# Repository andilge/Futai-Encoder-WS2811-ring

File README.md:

# A sparkfun enlighted RGB rotary encoder and a ring of 12 WS2811 F5 LEDs behind a translucent blank cover panel
The ultimate DIY human light controller interface plenty of colored LEDs.

## Credits
Inspired by [isotope-engineering's RGB rotary encoder](https://github.com/isotope-engineering/RGB-Encoder-Board "isotope-engineering's RGB rotary encoder").

Shoutout to [ezcGman](https://github.com/ezcGman "ezcGman") for the assistance with the KiCad symbols and footprints, hints about thermal reliefs on pads and the continuous feedback about his experiences while building up the circuit with the board.

## KiCad dependencies
This project uses custom KiCad symbols and footprints and 3D models. Follow folder 'libs' with all details.

## Parts list
The folder 'fabrication' contains the zipped production files for pcb ordering and interactive bill of material ibom.html with purchase links for the components.

Additional to this you can purchase 10 blank cover panels on [aliexpress.com](https://www.aliexpress.com/item/32884601740.html "aliexpress.com")

### SPECIAL ATTENTION REQUIRED !
*There are reports about wrong pin out for the addressable LEDs (D1-D12)*

The [official data sheet from the producer](http://cn.world-semi.com/DownLoadFile/98 "official data sheet from the producer") says
|  pin # |   description   |
|:------:|:---------------:|
|   1    |       DOUT      |
|   2    |       VCC       |
|   3    |       GND       |
|   4    |       DIN       |

With the purchase URL in the BOM, you might get LEDs with 180 degree flipped around pin out
|  pin # |   description   |
|:------:|:---------------:|
|   1    |       DIN       |
|   2    |       GND       |
|   3    |       VCC       |
|   4    |       DOUT      |

If you solder these faulty LEDs on the board "the right way around" the following will happen:
No light turns on and the LEDs instantly burn off to nirvana, some with, others without magic smoke :astonished: rip

The board continues following the LED's specification and can handle these faulty LEDs if you just place them "the wrong way around". Basically, flipped pins together with flipped placement turns out as success again :man_facepalming:.

**IMPORTANT**: Please test a LED from the sent bunch first to get a reality approach about which way around you should use them !

Special thanks to [ezcGman](https://github.com/ezcGman "ezcGman") for burning time and components to achieve this particular insight.

## Connector pinout
| silkscreen | description                                                                                |
|:----------:|--------------------------------------------------------------------------------------------|
| 5V         | 5 Volt                                                                                     |
| GND        | Ground                                                                                     |
| EncA       | Encoder A                                                                                  |
| EncB       | Encoder B                                                                                  |
| SW         | Switch. On pressing the switch, 3.3 Volt are being passed to this header pin.              |
| RED        | High voltage level red channel for the rotary encoder LED. *See more information below !   |
| GRE        | High voltage level green channel for the rotary encoder LED. *See more information below ! |
| BLU        | High voltage level blue channel for the rotary encoder LED. *See more information below !  |
| Din        | Data bus in for the adressable LEDs                                                        |
| Dout       | Data bus out for the adressable LEDs                                                       |

*For compatibility reasons with RGB strips, the board exptects 24V (also dimmed with pwm) at the rgb pin headers. If you're driving your **strip with 12V**, please change the value for **R51, R61 and R71 to 5.1kΩ**.

## Schematic
Dive deeper into technical details in the folder 'datasheets-and-schematic'.

## Tools list
### Required
- A soldering iron
- Solder

### Optional
- For SMD components and addressable LEDs:
  - A hot air soldering/re-flow station. However, the smallest parts are 0805 SMD components which can be soldered with a soldering iron. The LED's legs are very close together and easier to solder with hot air.
  - Solder paste
- Tweezers
- The famous IKEA cork coaster (Onderzetter) that gently takes up the heat of your soldering tools.

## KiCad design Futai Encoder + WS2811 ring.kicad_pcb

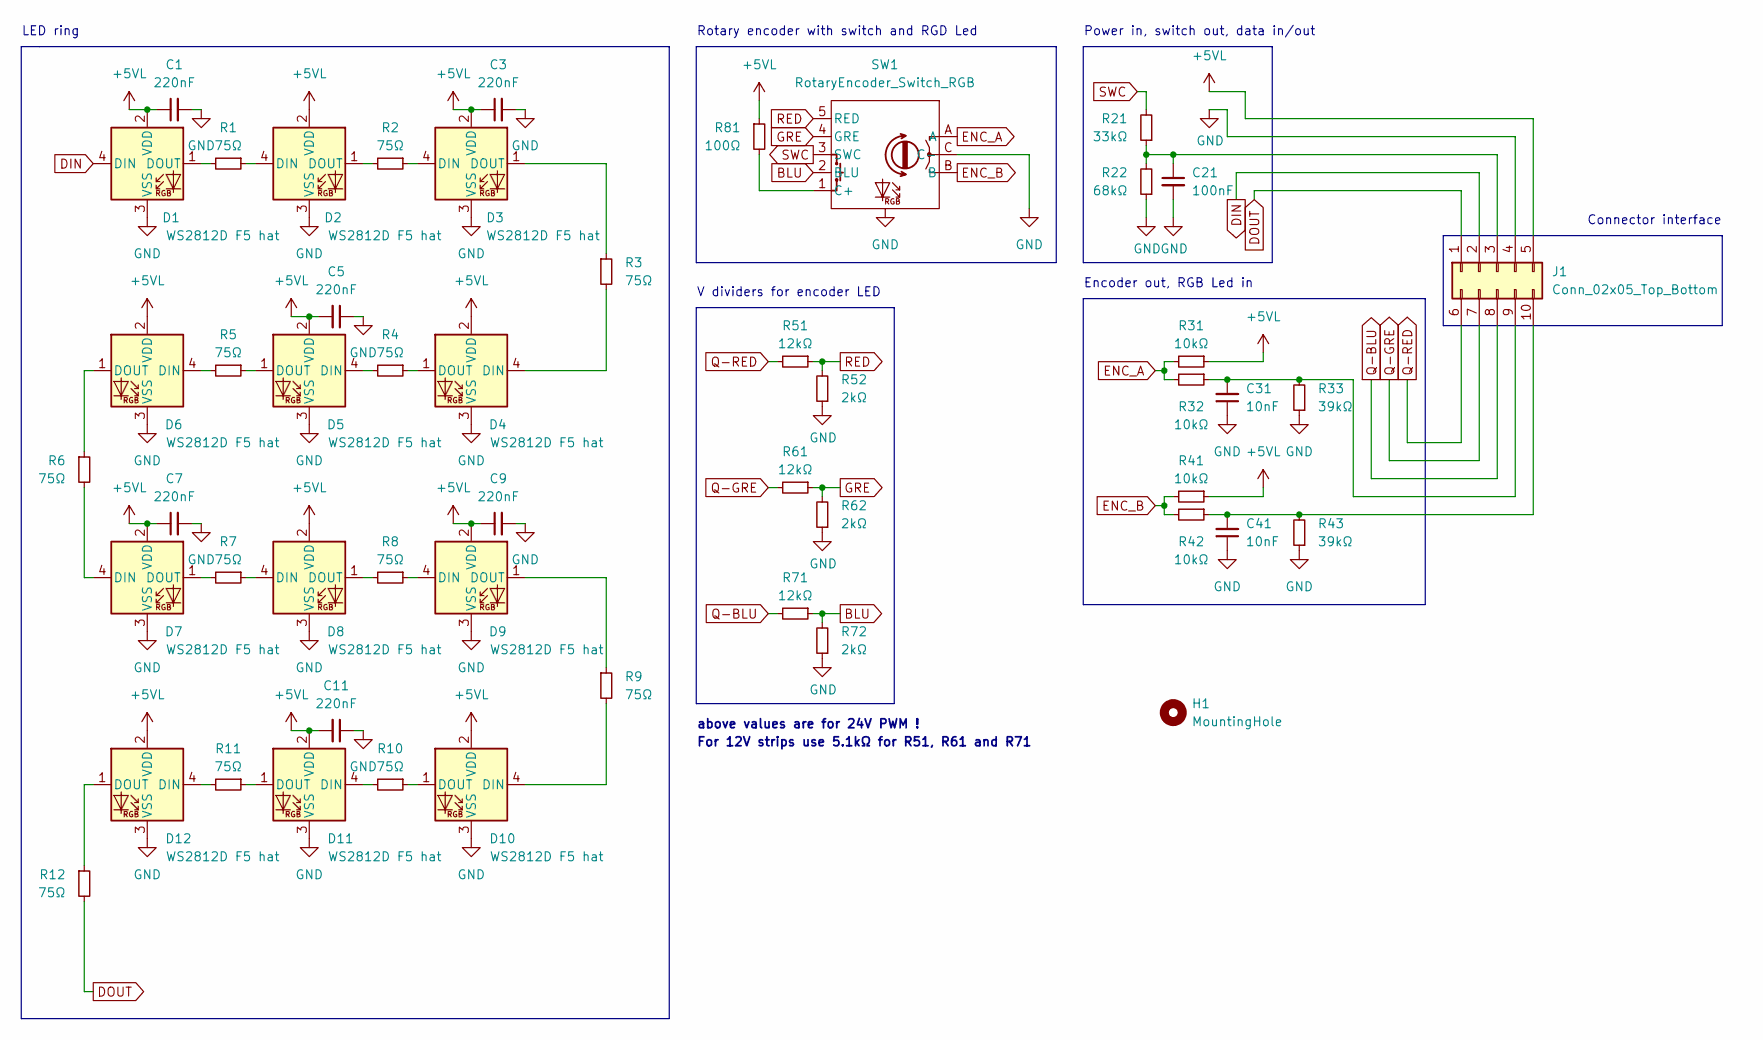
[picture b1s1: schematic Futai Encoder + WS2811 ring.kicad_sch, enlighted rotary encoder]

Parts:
C1, C3, C5, C7, C9, C11: 220nF; C_0805_2012Metric
C21: 100nF; C_0805_2012Metric
C31, C41: 10nF; C_0805_2012Metric
D1, D2, D3, D4, D5, D6, D7, D8, D9, D10, D11, D12: WS2812D F5 hat; WS2811D-F5-1261
H1: MountingHole; MountingHole_2.2mm_M2
J1: Conn_02x05_Top_Bottom; PinHeader_2x05_P2.54mm_Vertical
R1, R2, R3, R4, R5, R6, R7, R8, R9, R10, R11, R12: 75Ω; R_0805_2012Metric
R21: 33kΩ; R_0805_2012Metric
R22: 68kΩ; R_0805_2012Metric
R31, R32, R41, R42: 10kΩ; R_0805_2012Metric
R33, R43: 39kΩ; R_0805_2012Metric
R51, R61, R71: 12kΩ; R_0805_2012Metric
R52, R62, R72: 2kΩ; R_0805_2012Metric
R81: 100Ω; R_0805_2012Metric
SW1: RotaryEncoder_Switch_RGB; LED_RotaryEncoder_EC12_Switch_Vertical_H20mm

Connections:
+5VL: C1.1, C3.1, C5.2, C7.1, C9.1, C11.2, D1.2 (VDD), D2.2 (VDD), D3.2 (VDD), D4.2 (VDD), D5.2 (VDD), D6.2 (VDD), D7.2 (VDD), D8.2 (VDD), D9.2 (VDD), D10.2 (VDD), D11.2 (VDD), D12.2 (VDD), J1.5, R31.1, R41.1, R81.1
BLU: R71.1, R72.2, SW1.2 (BLU)
DIN: D1.4 (DIN), J1.2
DOUT: J1.1, R12.2
ENC_A: R31.2, R32.2, SW1.A
ENC_B: R41.2, R42.2, SW1.B
GND: C1.2, C3.2, C5.1, C7.2, C9.2, C11.1, C21.2, C31.1, C41.1, D1.3 (VSS), D2.3 (VSS), D3.3 (VSS), D4.3 (VSS), D5.3 (VSS), D6.3 (VSS), D7.3 (VSS), D8.3 (VSS), D9.3 (VSS), D10.3 (VSS), D11.3 (VSS), D12.3 (VSS), J1.4, R22.1, R33.1, R43.1, R52.1, R62.1, R72.1, SW1.C (C-)
GRE: R61.1, R62.2, SW1.4 (GRE)
unnamed: C21.1, J1.3, R21.1, R22.2
unnamed: C31.2, J1.9, R32.1, R33.2
unnamed: C41.2, J1.10, R42.1, R43.2
unnamed: D1.1 (DOUT), R1.2
unnamed: D2.1 (DOUT), R2.2
unnamed: D2.4 (DIN), R1.1
unnamed: D3.1 (DOUT), R3.1
unnamed: D3.4 (DIN), R2.1
unnamed: D4.1 (DOUT), R4.1
unnamed: D4.4 (DIN), R3.2
unnamed: D5.1 (DOUT), R5.1
unnamed: D5.4 (DIN), R4.2
unnamed: D6.1 (DOUT), R6.1
unnamed: D6.4 (DIN), R5.2
unnamed: D7.1 (DOUT), R7.2
unnamed: D7.4 (DIN), R6.2
unnamed: D8.1 (DOUT), R8.2
unnamed: D8.4 (DIN), R7.1
unnamed: D9.1 (DOUT), R9.1
unnamed: D9.4 (DIN), R8.1
unnamed: D10.1 (DOUT), R10.1
unnamed: D10.4 (DIN), R9.2
unnamed: D11.1 (DOUT), R11.1
unnamed: D11.4 (DIN), R10.2
unnamed: D12.1 (DOUT), R12.1
unnamed: D12.4 (DIN), R11.2
unnamed: R81.2, SW1.1 (C+)
Q-BLU: J1.8, R71.2
Q-GRE: J1.7, R61.2
Q-RED: J1.6, R51.2
RED: R51.1, R52.2, SW1.5 (RED)
SWC: R21.2, SW1.3 (SWC)

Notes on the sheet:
For 12V strips use 5.1kΩ for R51, R61 and R71
LED ring
Rotary encoder with switch and RGD Led
Power in, switch out, data in/out
above values are for 24V PWM !
Encoder out, RGB Led in
V dividers for encoder LED
Connector interface

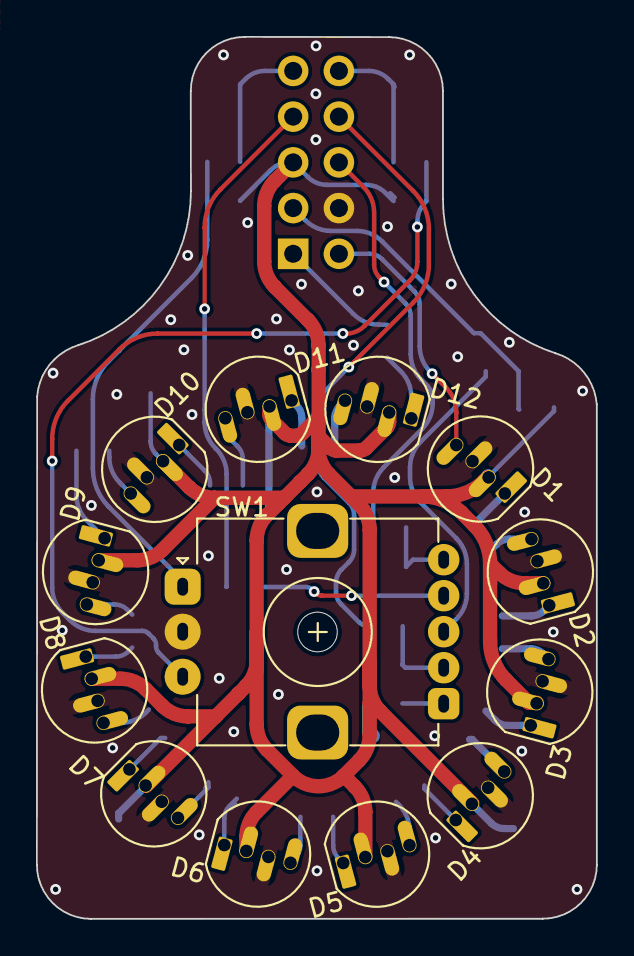
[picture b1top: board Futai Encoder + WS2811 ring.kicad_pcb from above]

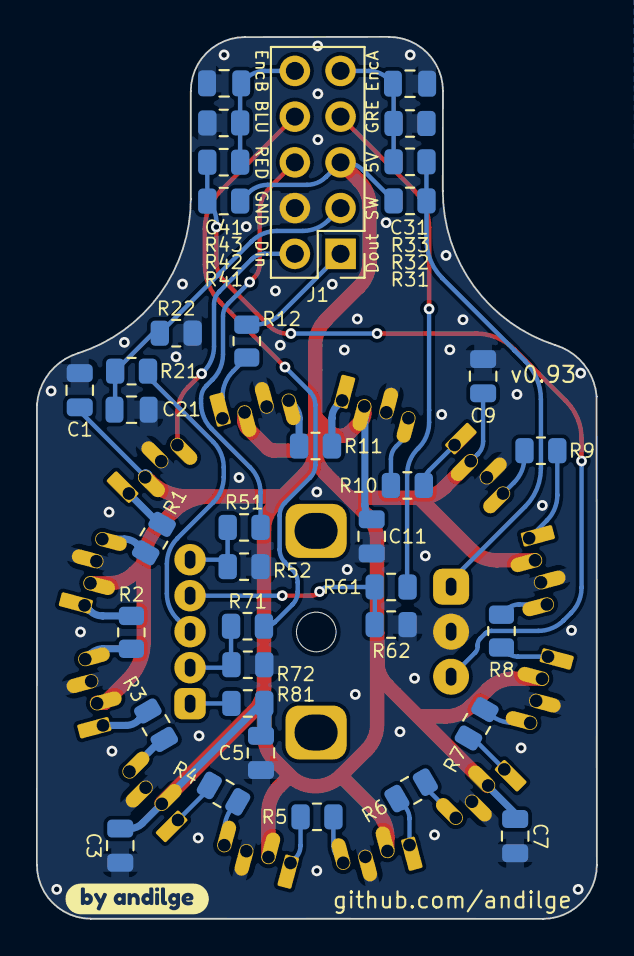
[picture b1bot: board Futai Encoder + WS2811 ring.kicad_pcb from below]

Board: 2 copper layers, 31.1 x 49.0 mm, 52 parts (38 on the bottom side), 40 nets.

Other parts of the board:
kibuzzard-6202B283: G***; kibuzzard-6202B283

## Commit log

2022-01-02 small cosmetic changes
2022-01-02 fix image in README.md
2022-01-02 brushing up README.md
2022-01-02 brushing up README.md 2
2022-01-03 smaller board width, new component placements and better track routing
2022-01-03 brushing up credits in README.md
2022-01-04 fixing wrong header pin descrition on borad
2022-01-04 completeing 3d models, adding new images
2022-01-04 fixing offset on 3ds and new immages
2022-01-04 fixing offset on 3ds and new immages 2
2022-01-04 new 3d for encoder, fixing ibom.html + new images
2022-01-18 Clarified the silkscreen to know LED orientation
2022-01-18 adding v0.7
2022-01-18 cleaning up old footprint
2022-01-18 adding fabrication files for 0.7
2022-01-19 lowering value for R1-R12
2022-01-19 small change to value R1-R12
2022-01-19 special note for D1-D12 in README.md
2022-01-19 small brush up in README.md
2022-01-19 small brush up in README.md 2
2022-01-19 small brush up in README.md 3
2022-01-19 small brush up in README.md 4
2022-01-19 small brush up in README.md 5
2022-01-19 small brush up in README.md 6
2022-01-20 v0.8
2022-01-20 changing name plate to panel in README.md
2022-01-22 v0.9
2022-01-22 better edge cut, adding more info to README.md
2022-01-29 encoder with shorter handle
2022-01-29 handsolder friendly footprint for LEDs
2022-01-29 new images with the new LEd footpring
2022-01-31 adding M3 hole beneth encoder to mark drill hole on panel
2022-01-31 adding fabrication files v0.92, smal improvment README.md
2022-02-07 brushing up schematic diagram.pdf
2022-02-08 smaller silkscreens, minor changes in trackings
2022-02-10 fixing typo
2022-02-24 v0.93, minor routing changes, better gnd zones
2022-02-27 smaller center hole
2024-01-23 Update README.md
    rot enc, futai -> sparkfun
